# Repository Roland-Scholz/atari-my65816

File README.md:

# atari-my65816
Sources for my65816 FPGA computer

I am mainly working on this project because I want to fool around with FPGA
The aim was to implement a 65816 machine which uses a OS like the one found in the Atari XL/XE.
Apart from the basic (kernel)-OS, nothing is compatible or even like the original Atari XL/XE series.

- homemade 65816 FPGA core, running at 100Mhz, not state compatible
- 8MB SD-RAM, running at 100Mhz
- RGB (Scart) output
- Resolutions:
	- 320x200 graphics 256 out of 512 colors
	- 640x200 graphics 2 / 512 colors
	-  80x25  Text 2/512 colors
	-  80x25  Text 16 forground, 16 background colors
	-  8 sprites 24x200 pixel 16/256 colors2
- 2 x RS232: Terminal 115200 baud, Mouse 1200 Baud
- PS/2 keyboard interface
- SD-Card interface
- 4x7seg display
- beeper
- 1 reset, 4 buttons

- Atari-like kernel/monitor, Fat16-DOS
- VTL-2 with 24-bit enhancements, load and save command

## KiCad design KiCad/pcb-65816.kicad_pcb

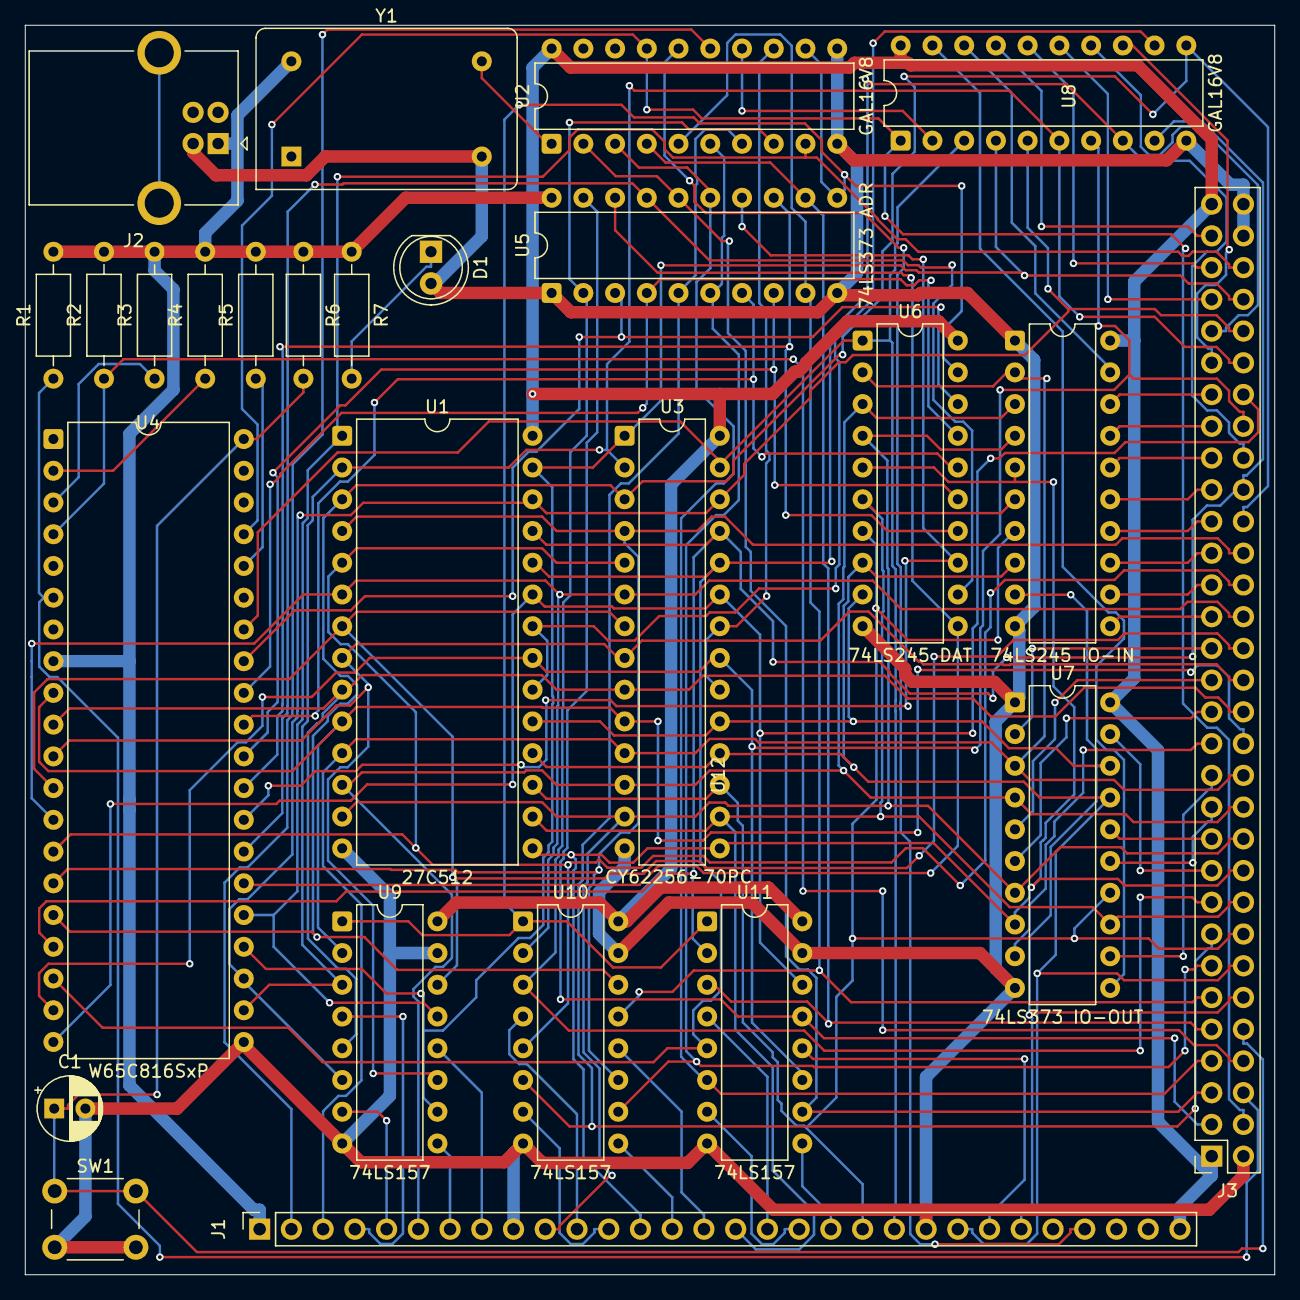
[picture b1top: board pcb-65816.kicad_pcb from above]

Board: 2 copper layers, 100.0 x 100.0 mm, 26 parts (0 on the bottom side), 93 nets.

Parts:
C1: C_Polarized; CP_Radial_D5.0mm_P2.50mm
D1: LED; LED_D5.0mm_Clear
J1: Conn_01x30_Socket; PinSocket_1x30_P2.54mm_Vertical
J2: USB_B; USB_B_OST_USB-B1HSxx_Horizontal
J3: Conn_02x31_Odd_Even; PinSocket_2x31_P2.54mm_Vertical
R1, R2, R3, R4, R5, R6, R7: R; R_Axial_DIN0207_L6.3mm_D2.5mm_P10.16mm_Horizontal
SW1: SW_Push; SW_PUSH_6mm
U1: 27C512; DIP-28_W15.24mm
U2, U8: GAL16V8; DIP-20_W7.62mm
U3: CY62256-70PC; DIP-28_W7.62mm
U4: W65C816SxP; DIP-40_W15.24mm
U5: 74LS373 ADR; DIP-20_W7.62mm
U6: 74LS245 DAT; DIP-20_W7.62mm
U7: 74LS373 IO-OUT; DIP-20_W7.62mm
U9, U10, U11: 74LS157; DIP-16_W7.62mm
U12: 74LS245 IO-IN; DIP-20_W7.62mm
Y1: CXO_DIP14; Oscillator_DIP-14

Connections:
A0: J3.28, U1.10 (A0), U3.10 (A0), U4.9 (A0), U9.2 (I0a)
A1: J3.30, U1.9 (A1), U3.9 (A1), U4.10 (A1), U9.5 (I0b)
A2: J3.32, U1.8 (A2), U3.8 (A2), U4.11 (A2), U9.11 (I0c)
A3: J3.34, U1.7 (A3), U3.7 (A3), U4.12 (A3), U9.14 (I0d)
A4: J3.36, U1.6 (A4), U3.6 (A4), U4.13 (A4), U10.2 (I0a)
A5: J3.38, U1.5 (A5), U3.5 (A5), U4.14 (A5), U10.5 (I0b)
A6: J3.40, U1.4 (A6), U3.4 (A6), U4.15 (A6), U10.11 (I0c)
A7: J3.42, U1.3 (A7), U3.3 (A7), U4.16 (A7), U8.11 (I10/~OE), U10.14 (I0d)
A8: J3.44, U1.25 (A8), U3.25 (A8), U4.17 (A8), U8.9 (I9), U11.2 (I0a)
A9: J3.46, U1.24 (A9), U3.24 (A9), U4.18 (A9), U8.8 (I8), U11.5 (I0b)
A10: J3.48, U1.21 (A10), U3.21 (A10), U4.19 (A10), U8.7 (I7), U11.11 (I0c)
A11: J3.50, U1.23 (A11), U3.23 (A11), U4.20 (A11), U11.14 (I0d)
A12: J3.52, U1.2 (A12), U3.2 (A12), U4.22 (A12), U8.6 (I6), U9.3 (I1a)
A13: J3.54, U1.26 (A13), U3.26 (A13), U4.23 (A13), U8.5 (I5), U9.6 (I1b)
A14: J3.56, U1.27 (A14), U3.1 (A14), U4.24 (A14), U8.4 (I4), U9.10 (I1c)
A15: J3.58, U1.1 (A15), U2.9 (I9), U4.25 (A15), U9.13 (I1d)
A16: J3.17, U2.8 (I8), U5.2 (O0), U10.3 (I1a)
A17: J3.15, U2.7 (I7), U5.5 (O1), U10.6 (I1b)
A18: J3.13, U2.6 (I6), U5.6 (O2), U10.10 (I1c)
A19: J3.11, U2.5 (I5), U5.9 (O3), U10.13 (I1d)
A20: J3.9, U2.4 (I4), U5.12 (O4), U11.3 (I1a)
A21: J3.7, U2.3 (I3), U5.15 (O5), U11.6 (I1b)
A22: J3.5, U2.2 (I2), U5.16 (O6), U11.10 (I1c)
A23: J3.3, U5.19 (O7), U11.13 (I1d)
BA0: U4.33 (D0), U5.3 (D0), U6.18 (B0)
BA1: U4.32 (D1), U5.4 (D1), U6.17 (B1)
BA2: U4.31 (D2), U5.7 (D2), U6.16 (B2)
BA3: U4.30 (D3), U5.8 (D3), U6.15 (B3)
BA4: U4.29 (D4), U5.13 (D4), U6.14 (B4)
BA5: U4.28 (D5), U5.14 (D5), U6.13 (B5)
BA6: U4.27 (D6), U5.17 (D6), U6.12 (B6)
BA7: U4.26 (D7), U5.18 (D7), U6.11 (B7)
CAS\: J1.2, U2.15 (IO5)
CLK: U2.1 (I1/CLK), Y1.8 (OUT)
CLK3: J3.4, U2.17 (I03), U4.37 (ϕ0), U8.1 (I1/CLK)
CLK3\: U2.12 (IO8), U5.11 (LE), U6.19 (CE), U9.1 (S), U10.1 (S), U11.1 (S)
D0: J1.3, J3.26, U1.11 (D0), U3.11 (Q0), U6.2 (A0), U7.3 (D0), U12.2 (A0)
D1: J1.6, J3.24, U1.12 (D1), U3.12 (Q1), U6.3 (A1), U7.4 (D1), U12.3 (A1)
D2: J1.10, J3.22, U1.13 (D2), U3.13 (Q2), U6.4 (A2), U7.7 (D2), U12.4 (A2)
D3: J1.13, J3.20, U1.15 (D3), U3.15 (Q3), U6.5 (A3), U7.8 (D3), U12.5 (A3)
D4: J1.16, J3.18, U1.16 (D4), U3.16 (Q4), U6.6 (A4), U7.13 (D4), U12.6 (A4)
D5: J1.20, J3.16, U1.17 (D5), U3.17 (Q5), U6.7 (A5), U7.14 (D5), U12.7 (A5)
D6: J1.23, J3.14, U1.18 (D6), U3.18 (Q6), U6.8 (A6), U7.17 (D6), U12.8 (A6)
D7: J1.25, J3.12, U1.19 (D7), U3.19 (Q7), U6.9 (A7), U7.18 (D7), U12.9 (A7)
DA0: J1.4, U9.4 (Za)
DA1: J1.5, U9.7 (Zb)
DA2: J1.7, U9.9 (Zc)
DA3: J1.8, U9.12 (Zd)
DA4: J1.11, U10.4 (Za)
DA5: J1.12, U10.7 (Zb)
DA6: J1.14, U10.9 (Zc)
DA7: J1.15, U10.12 (Zd)
DA8: J1.17, U11.4 (Za)
DA9: J1.18, U11.7 (Zb)
DA10: J1.19, U11.9 (Zc)
DA11: J1.24, U11.12 (Zd)
GND: C1.2, D1.2 (A), J1.9, J1.22, J2.4 (GND), J3.2, J3.60, J3.62, SW1.2, U1.14 (GND), U2.10 (GND), U2.11 (I10/~OE), U3.14 (GND), U4.21 (VSS), U5.1 (OE), U5.10 (GND), U6.10 (GND), U7.1 (OE), U7.10 (GND), U8.10 (GND), U9.8 (GND), U9.15 (E), U10.8 (GND), U10.15 (E), U11.8 (GND), U11.15 (E), U12.1 (A->B), U12.10 (GND), Y1.7 (GND)
I0: J3.49, U12.18 (B0)
I1: J3.47, U12.17 (B1)
I2: J3.45, U12.16 (B2)
I3: J3.43, U12.15 (B3)
I4: J3.41, U12.14 (B4)
I5: J3.39, U12.13 (B5)
I6: J3.37, U12.12 (B6)
I7: J3.35, U12.11 (B7)
IO0\: U7.11 (LE), U8.19 (IO1)
IO1\: U8.18 (IO2), U12.19 (CE)
IO2\: J3.59, U8.17 (I03)
IO3\: J3.57, U8.16 (IO4)
IO4\: J3.55, U8.15 (IO5)
IO5\: J3.53, U8.14 (IO6)
IO6\: J3.51, U8.13 (IO7)
IRQ\: J3.8, R2.1, U4.4 (~IRQ)
NMI\: J3.6, R1.1, U4.6 (~NMI)
unnamed: D1.1 (K), R7.2
unnamed: R5.1, U4.36 (BE)
unnamed: R4.1, U4.2 (RDY)
unnamed: R3.1, U4.3 (~ABORT)
O0: J3.33, U7.2 (O0)
O1: J3.31, U7.5 (O1)
O2: J3.29, U7.6 (O2)
O3: J3.27, U7.9 (O3)
O4: J3.25, U7.12 (O4)
O5: J3.23, U7.15 (O5)
O6: J3.21, U7.16 (O6)
O7: J3.19, U7.19 (O7)
RAM\: U2.13 (IO7), U3.20 (~CS), U3.22 (~OE)
RAS\: J1.27, U2.16 (IO4)
RES\: C1.1, J3.10, R6.2, SW1.1, U4.40 (~RES)
ROMIO\: U2.14 (IO6), U8.2 (I2)
ROM\: U1.20 (~CE), U1.22 (~OE), U8.12 (IO8)
R/W\: J1.21, U3.27 (~WE), U4.34 (R/~W), U6.1 (A->B), U8.3 (I3)
VCC: J1.1, J1.30, J2.1 (VBUS), J3.1, J3.61, R1.2, R2.2, R3.2, R4.2, R5.2, R6.1, R7.1, U1.28 (VCC), U2.20 (VCC), U3.28 (VCC), U4.8 (VDD), U5.20 (VCC), U6.20 (VCC), U7.20 (VCC), U8.20 (VCC), U9.16 (VCC), U10.16 (VCC), U11.16 (VCC), U12.20 (VCC), Y1.14 (Vcc)

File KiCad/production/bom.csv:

Designator,Footprint,Quantity,Value,LCSC Part #
C1,CP_Radial_D5.0mm_P2.50mm,1,C_Polarized,
D1,LED_D5.0mm_Clear,1,LED,
J1,PinSocket_1x30_P2.54mm_Vertical,1,Conn_01x30_Socket,
J2,USB_B_OST_USB-B1HSxx_Horizontal,1,USB_B,
J3,PinSocket_2x31_P2.54mm_Vertical,1,Conn_02x31_Odd_Even,
"R1, R2, R3, R4, R5, R6, R7",R_Axial_DIN0207_L6.3mm_D2.5mm_P10.16mm_Horizontal,7,R,
SW1,SW_PUSH_6mm,1,SW_Push,
U1,DIP-28_W15.24mm,1,27C512,
"U10, U11, U9",DIP-16_W7.62mm,3,74LS157,
U12,DIP-20_W7.62mm,1,74LS245 IO-IN,
"U2, U8",DIP-20_W7.62mm,2,GAL16V8,
U3,DIP-28_W7.62mm,1,CY62256-70PC,
U4,DIP-40_W15.24mm,1,W65C816SxP,
U5,DIP-20_W7.62mm,1,74LS373 ADR,
U6,DIP-20_W7.62mm,1,74LS245 DAT,
U7,DIP-20_W7.62mm,1,74LS373 IO-OUT,
Y1,Oscillator_DIP-14,1,CXO_DIP14,

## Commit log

2022-06-06 kernel FPGA working
2022-06-06 .gitignore
2022-06-06 FPGA+Emulator
2022-06-06 del release
2025-03-30 kernelWDC
